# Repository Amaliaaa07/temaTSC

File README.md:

# temaTSC
smartwatch

## BOM (Bill of Materials)

| Referință | Componentă | Descriere | Cantitate | Link JLC | Datasheet |
|-----------|-----------|-------------------|-----------|----------|-----------|
| U1          | MCU             | nRF52840               | 1         | [JLC](https://jlcpcb.com/partdetail/NordicSemiconductor-nRF52840_QIAA/C190794) | [Datasheet](https://4donline.ihs.com/images/VipMasterIC/IC/NRSA/NRSA-S-A0021008244/NRSA-S-A0021008244-1.pdf?hkey=61A2E4C270F0397D049F8F05BD4F1054)  |
| IC1         | LiPo Charger    | BQ25180YBGR            | 1         | [JLC](https://componentsearchengine.com/prices/BQ25180YBGR?manufacturer=Texas%20Instruments)     | [Datasheet](https://www.ti.com/lit/ds/symlink/bq25180.pdf)                                                     |
| IC2         | Haptic Driver   | DRV2605YZFR            | 1         | [JLC](https://componentsearchengine.com/prices/DRV2605YZFR?manufacturer=Texas%20Instruments)     | [Datasheet](https://www.ti.com/lit/ds/symlink/drv2605.pdf)                                                     |
| IC3         | IMU             | BMA423                 | 1         | [JLC](https://componentsearchengine.com/prices/BMA423?manufacturer=BOSCH)                      | [Datasheet](https://4donline.ihs.com/images/VipMasterIC/IC/BSCH/BSCH-S-A0007921771/BSCH-S-A0010021471-1.pdf?hkey=61A2E4C270F0397D049F8F05BD4F1054)    |
| IC9         | DC/DC Converter | RT6160AWSC             | 1         | [JLC](https://componentsearchengine.com/prices/RT6160AWSC?manufacturer=RICHTEK)               | [Datasheet](https://4donline.ihs.com/images/VipMasterIC/IC/RHTK/RHTK-S-A0025617216/RHTK-S-A0025617221-1.pdf?hkey=61A2E4C270F0397D049F8F05BD4F1054)                                |
| U3          | Fuel Gauge      | MAX17048G+T10          | 1         | [JLC](https://componentsearchengine.com/prices/MAX17048G%2BT10?manufacturer=Analog%20Devices)      | [Datasheet](https://4donline.ihs.com/images/VipMasterIC/IC/RHTK/RHTK-S-A0025617216/RHTK-S-A0025617221-1.pdf?hkey=61A2E4C270F0397D049F8F05BD4F1054)         |
| D3          | ESD Protection  | USBLC6-2SC6Y           | 1         | [JLC](https://componentsearchengine.com/prices/USBLC6-2SC6Y?manufacturer=STMicroelectronics)   | [Datasheet](https://www.analog.com/media/en/technical-documentation/data-sheets/MAX17048-MAX17049.pdf?ADICID=SYND_WW_P682800_PF-spglobal)                                             |
| J4          | USB-C Connector | KH-TYPE-C-16P          | 1         | [JLC](https://www.snapeda.com/parts/KH-TYPE-C-16P/kinghelm/view-part/?ref=search&t=KH-TYPE-C-16P&ab_test_case=b)                    | [Datasheet](https://www.snapeda.com/parts/KH-TYPE-C-16P/kinghelm/datasheet/)        |
| J1          | E-Paper Connector | 503480-2400E         | 1         | [JLC](https://componentsearchengine.com/prices/5034802400?manufacturer=Molex)                 | [Datasheet](https://4donline.ihs.com/images/VipMasterIC/IC/MOLE/MOLE-S-A0003522481/MOLE-S-A0010982248-1.pdf?hkey=61A2E4C270F0397D049F8F05BD4F1054)                                      |
| ANT1        | Antena BLE      | 2450AT18B100E          | 1         | [JLC](https://componentsearchengine.com/prices/2450AT18B100E?manufacturer=JOHANSON%20TECHNOLOGY)             | [Datasheet](https://www.johansontechnology.com/docs/1187/2450AT18B100_X8XXogU.pdf)                     |
| X1          | Crystal 32MHz   | SMD 2016               | 1         | [JLC](https://componentsearchengine.com/prices/SMD2016B050TF?manufacturer=Yageo%20Group)                   | [Datasheet](https://4donline.ihs.com/images/VipMasterIC/IC/YAGO/YAGO-S-A0024580626/YAGO-S-A0024591343-1.pdf?hkey=61A2E4C270F0397D049F8F05BD4F1054)                            |
| X2          | Crystal 32.768kHz | SMD 2016             | 1         | [JLC](https://componentsearchengine.com/prices/SMD2016B050TF?manufacturer=Yageo%20Group)               | [Datasheet](https://4donline.ihs.com/images/VipMasterIC/IC/YAGO/YAGO-S-A0024580626/YAGO-S-A0024591343-1.pdf?hkey=61A2E4C270F0397D049F8F05BD4F1054)                               |
| SW1-3       | Buton tactil    | EVP-AKE31A             | 3         | [JLC](https://componentsearchengine.com/prices/EVP-AKE31A?manufacturer=Panasonic)               | [Datasheet](https://industrial.panasonic.com/cdbs/www-data/pdf/ATK0000/ATK0000C434.pdf)                        |
| J2          | SWD Connector   | TC2030-IDC             | 1         | [JLC](https://componentsearchengine.com/prices/TC2030-IDC?manufacturer=Tag%20Connect)             | [Datasheet](https://4donline.ihs.com/images/VipMasterIC/IC/TGCN/TGCN-S-A0008988129/TGCN-S-A0008988129-1.pdf?hkey=61A2E4C270F0397D049F8F05BD4F1054)                   |
| Q2          | MOSFET P-ch     | DMG2305UX-7            | 1         | [JLC](https://componentsearchengine.com/prices/DMG2305UX-7?manufacturer=Diodes%20Incorporated)                 | [Datasheet](https://4donline.ihs.com/images/VipMasterIC/IC/DIOD/DIOD-S-A0013043571/DIOD-S-A0013120650-1.pdf?hkey=61A2E4C270F0397D049F8F05BD4F1054)                                            |
| Q3          | MOSFET N-ch     | SI1308EDL-T1-GE3       | 1         | [JLC](https://componentsearchengine.com/prices/Si1308EDL-T1-GE3?manufacturer=Vishay)             | [Datasheet](https://4donline.ihs.com/images/VipMasterIC/IC/VISH/VISH-S-A0000692786/VISH-S-A0000692786-1.pdf?hkey=61A2E4C270F0397D049F8F05BD4F1054)                                                   |
| D2, D4, D5  | Dioda Schottky  | MBR0530                | 3         | [JLC](https://componentsearchengine.com/prices/MBR0530?manufacturer=MCC)           | [Datasheet](https://4donline.ihs.com/images/VipMasterIC/IC/MCCC/MCCCS04194/MCCCS04194-1.pdf?hkey=61A2E4C270F0397D049F8F05BD4F1054)                                         |
| L1          | Inductanta 0.47µH | FTC252012SR47MBCA    | 1         | [JLC](https://jlcpcb.com/partdetail/6763488-FTC252012SR47MBCA/C5832368)                 |
| L2          | Inductanta 15nH | RF matching 0201       | 1         | [JLC](https://jlcpcb.com/partdetail/Sunlord-SDCL0201C15NJTDF/C389547)          |     -                   |
| L3          | Inductanta 3.9nH | RF matching 0201      | 1         | [JLC](https://jlcpcb.com/partdetail/Sunlord-SDCL0201C3N9STDF/C389544)          |     -                   |
| L5          | Inductanta 68µH | EPD driver SMD         | 1         | [JLC](https://jlcpcb.com/partdetail/Sumida-CDMC4D28NP680MC/C408336)            |     -                       |
| L7          | Inductanta 10µH | DC/DC SMD              | 1         | [JLC](https://jlcpcb.com/partdetail/Sunlord-MWSA0402S100MT/C408352)            |     -                     |
| C*          | Condensatoare   | 100nF decuplare 0201   | multiple  | [JLC](https://jlcpcb.com/partdetail/Samsung-CL03B104KO3NNNC/C15195)            | -                                                                                                               |
| C*          | Condensatoare   | >100nF bulk 0402       | multiple  | [JLC](https://jlcpcb.com/partdetail/Samsung-CL05A475KP5NRNC/C25771)            | -                                                                                                               |
| R*          | Rezistente      | Diverse valori 0201    | multiple  | [JLC](https://jlcpcb.com/partdetail/UNI-ROYAL-0201WAF1001T5E/C17513)           | -                                                                                                               |

## Descrierea funcționalității hardware

### Microcontroller — nRF52840

Inima dispozitivului este **Nordic nRF52840**, un SoC (System on Chip) cu procesor ARM Cortex-M4 la 64 MHz, cu unitate FPU, 1 MB Flash, 256 KB RAM și radio Bluetooth 5.0 integrat. Chipul operează la 3.3V și gestionează toate perifericele prin interfețele SPI, I2C și GPIO.

### Alimentare

Lanțul de alimentare funcționează astfel:
- **USB-C (KH-TYPE-C-16P)** furnizează VBUS (5V) prin conectorul de încărcare
- **USBLC6-2SC6Y** protejează liniile D+/D- împotriva descărcărilor electrostatice (ESD)
- **BQ25180YBGR** este charger-ul LiPo care încarcă bateria de 3.7V și comunică cu MCU-ul prin I2C pentru a raporta starea încărcării. Curentul maxim de încărcare este de 350mA.
- **MAX17048G+T10** este fuel gauge-ul care măsoară tensiunea bateriei și estimează starea de încărcare (SoC) prin algoritmul ModelGauge, comunicând prin I2C. Generează o întrerupere ALERT când bateria scade sub un prag configurat.
- **RT6160AWSC** este un convertor DC/DC boost care generează tensiunea de 3.3V necesară MCU-ului și perifericelor din tensiunea bateriei. Frecvența de comutare este de 1.5MHz, folosind inductanța L7 de 10µH.

### Display E-Paper

Display-ul e-paper se conectează prin conectorul FFC **503480-2400** (24 pini). Interfața de comunicație este **SPI** (MOSI, SCK) împreună cu semnale de control GPIO:
- **EPD_CS** — chip select
- **EPD_DC** — selectare mod Data/Command
- **EPD_RST** — reset display
- **EPD_BUSY** — semnal de ocupat (MCU-ul așteaptă să devină LOW înainte de a trimite date noi)

Circuitul de drive al display-ului conține diode Schottky MBR0530, MOSFET-uri și inductanța L5 (68µH) pentru generarea tensiunilor ridicate necesare panoului e-paper (PREVGH pozitiv, PREVGL negativ). Marele avantaj al display-ului e-paper este consumul zero în standby — imaginea rămâne afișată fără alimentare (display bistabil).

### IMU — BMA421

Senzorul de mișcare **BMA421** de la Bosch este un accelerometru 3-axis cu consum ultra-redus, folosit pentru:
- Detectarea pașilor (pedometru integrat în hardware)
- Recunoașterea activității (mers, alergat, stat)
- Detectarea orientării dispozitivului
- Wake-up la mișcare (trezirea MCU-ului din sleep)

Comunică cu MCU-ul prin **I2C** la adresa 0x18 sau 0x19 (selectabilă prin pinul SDO). Generează întreruperi pe liniile **INT1** și **INT2** pentru a trezi MCU-ul la detectarea unor evenimente, fără a consuma energie în modul standby. Tensiunea de alimentare este 3.3V (VDDIO și VDD).

### Driver Haptic — DRV2605YZFR

**DRV2605YZFR** de la Texas Instruments este un driver pentru actuatoare haptice (LRA/ERM) cu bibliotecă internă de 123 de efecte de vibrație stocate în ROM. Comunică prin **I2C** la adresa 0x5A și este activat de MCU prin semnalul **HAPTIC_EN** (GPIO). Oferă feedback tactil utilizatorului la interacțiunile cu interfața (notificări, confirmare butoane etc.).

### Conectivitate BLE

Radio-ul BLE integrat în nRF52840 operează la 2.4GHz și suportă Bluetooth 5.0 cu rate de date de 1Mbps (LE 1M PHY) și 2Mbps (LE 2M PHY). Este conectat la antena **2450AT18B100E** de la Johanson Technology printr-o rețea de matching RF compusă din L2 (15nH), L3 (3.9nH) și condensatoare de 1pF. Antena este plasată la exteriorul PCB-ului, iar zona de sub antenă este decupată complet (fără cupru și fără trasee) pentru a nu degrada performanța RF.

### Butoane

Trei butoane tactile **EVP-AKE31A** de la Panasonic (SW_UP, SW_DN, SW_ENT) sunt conectate la GPIO-urile MCU-ului cu rezistențe de pull-up de 10kΩ. La apăsare, pinul GPIO este tras la GND. Butoanele sunt plasate pe marginea PCB-ului, aliniate cu orificiile fizice din carcasă.

### Debug SWD

Interfața de programare și depanare **SWD** este expusă prin conectorul **TC2030-IDC** (Tag-Connect 6-pin, fără găuri). Semnalele disponibile sunt SWDIO, SWDCLK, SWO (trace), RESET, 3.3V și GND. Toate sunt marcate pe silkscreen cu test pad-uri dedicate.

### Oscilatoare

- **Crystal 32 MHz** — oscilator principal pentru MCU și radio BLE, cu condensatoare de sarcină de 12pF. Conectat pe pinii dedicați P0.00/XL1 și P0.01/XL2.
- **Crystal 32.768 kHz** — oscilator pentru RTC (Real Time Clock), cu condensatoare de 12pF. Conectat pe pinii dedicați XC1 și XC2. Permite timekeeping precis în modul low power.

---

## Calcul consum de energie

| Componentă | Curent tipic | Mod |
|-----------|-------------|-----|
| nRF52840 | 4.8 mA | Activ CPU |
| nRF52840 | 0.4 µA | Deep sleep |
| nRF52840 | 5.3 mA | BLE advertising |
| BMA421 | 150 µA | Normal |
| BMA421 | 2 µA | Low power |
| DRV2605 | 9 mA | Activ |
| DRV2605 | 40 µA | Standby |
| MAX17048 | 23 µA | Activ |
| RT6160AWSC | ~50 µA | Quiescent |
| Display e-paper | ~26 mA | Refresh |
| Display e-paper | 0 mA | Standby (bistabil) |

**Estimare autonomie:** Cu o baterie LiPo de 200mAh, în modul normal de utilizare (MCU în sleep majoritatea timpului, refresh display de câteva ori pe zi, BLE advertising periodic), curentul mediu estimat este de aproximativ 1-2mA, rezultând o autonomie de **4-8 zile**.

## Pinii nRF52840 utilizați

| Pin nRF52840 | Semnal | Componentă | Interfață | Motiv |
|-------------|--------|-----------|-----------|-------|
| P0.00/XL1 | XL1 | Crystal 32MHz | XTAL | Pin dedicat oscilator principal |
| P0.01/XL2 | XL2 | Crystal 32MHz | XTAL | Pin dedicat oscilator principal |
| XC1, XC2 | - | Crystal 32.768kHz | XTAL | Pini RTC dedicați |
| P0.04 | EPD_CS | E-Paper | SPI CS | Chip select display |
| P0.05 | EPD_DC | E-Paper | GPIO | Data/Command select |
| P0.06 | MOSI | E-Paper | SPI | Date SPI |
| P0.07 | SCK | E-Paper | SPI | Clock SPI |
| P0.08 | EPD_RST | E-Paper | GPIO | Reset display |
| P0.09 | EPD_BUSY | E-Paper | GPIO | Busy signal display |
| P0.13 | D- | USB-C | USB | Linie date USB |
| P0.14 | D+ | USB-C | USB | Linie date USB |
| P0.25 | SDA | I2C bus | I2C | Date I2C (IMU, Haptic, Charger, FuelGauge) |
| P0.26 | SCL | I2C bus | I2C | Clock I2C |
| P0.27 | PMIC_INT | BQ25180 | GPIO | Întrerupere charger |
| P0.28 | ALERT | MAX17048 | GPIO | Alertă fuel gauge |
| P1.01 | HAPTIC_EN | DRV2605 | GPIO | Enable driver haptic |
| P1.02 | IMU_INT1 | BMA421 | GPIO | Întrerupere IMU 1 |
| P1.03 | IMU_INT2 | BMA421 | GPIO | Întrerupere IMU 2 |
| P1.04 | SW_UP | Buton UP | GPIO | Buton sus |
| P1.05 | SW_DN | Buton DOWN | GPIO | Buton jos |
| P1.06 | SW_ENT | Buton ENTER | GPIO | Buton enter |
| P0.18/RESET | RESET | SWD | SWD | Reset MCU |
| SWDCLK | SWDCLK | TC2030-IDC | SWD | Clock debug |
| SWDIO | SWDIO | TC2030-IDC | SWD | Date debug |
| P0.22 | SWO | TC2030-IDC | SWD | Trace output |
| ANT | RF | Antenă BLE | RF | Pin antenă dedicat |
| VBUS | VBUS | USB-C | Power | Detecție VBUS |

---

## Design log

### Probleme întâmpinate și decizii luate

**Erori Overlap (12) — Aprobate**: Cele 12 erori de overlap 
sunt de trei tipuri:

**Via-Smd Overlap (2)**: Via-uri care se suprapun ușor 
  cu pad-uri SMD în zone aglomerate ale PCB-ului. Mutarea 
  acestora ar compromite rutarea semnalelor din zonă.

**Solid Polygon Shape-Pad Overlap (2)**: Pad-ul 
  termal al unui circuit integrat se suprapune ușor 
  cu conturul (courtyard) componentei vecine. 
  Suprapunerea este minimă și nu afectează 
  funcționalitatea electrică sau asamblarea, 
  deoarece componentele nu se suprapun fizic.

**Smd-Via Overlap (6)**: Via-uri plasate în apropierea 
  pad-urilor SMD în zone aglomerate ale PCB-ului. Acestea 
  sunt necesare pentru rutarea semnalelor și nu pot fi 
  mutate fără a compromite rutarea generală. Suprapunerea 
  este minimă și nu afectează funcționalitatea electrică 
  sau procesul de fabricație.

**Modelele 3D**
Componentele mici (rezistențe 0201, condensatoare 0201/0402) nu au modele 3D individuale asociate și folosesc modelul generic din Fusion 360. Componentele principale (nRF52840, BQ25180, conectorul USB-C, butoanele, cristalele) au modele 3D reale asociate.

---

## Imagini

Randările PCB-ului și ale dispozitivului complet se găsesc în folderul `/Images`.

---

## Licență

Acest proiect este licențiat sub licența **Apache 2.0**. Vezi fișierul [LICENSE](LICENSE) pentru detalii.

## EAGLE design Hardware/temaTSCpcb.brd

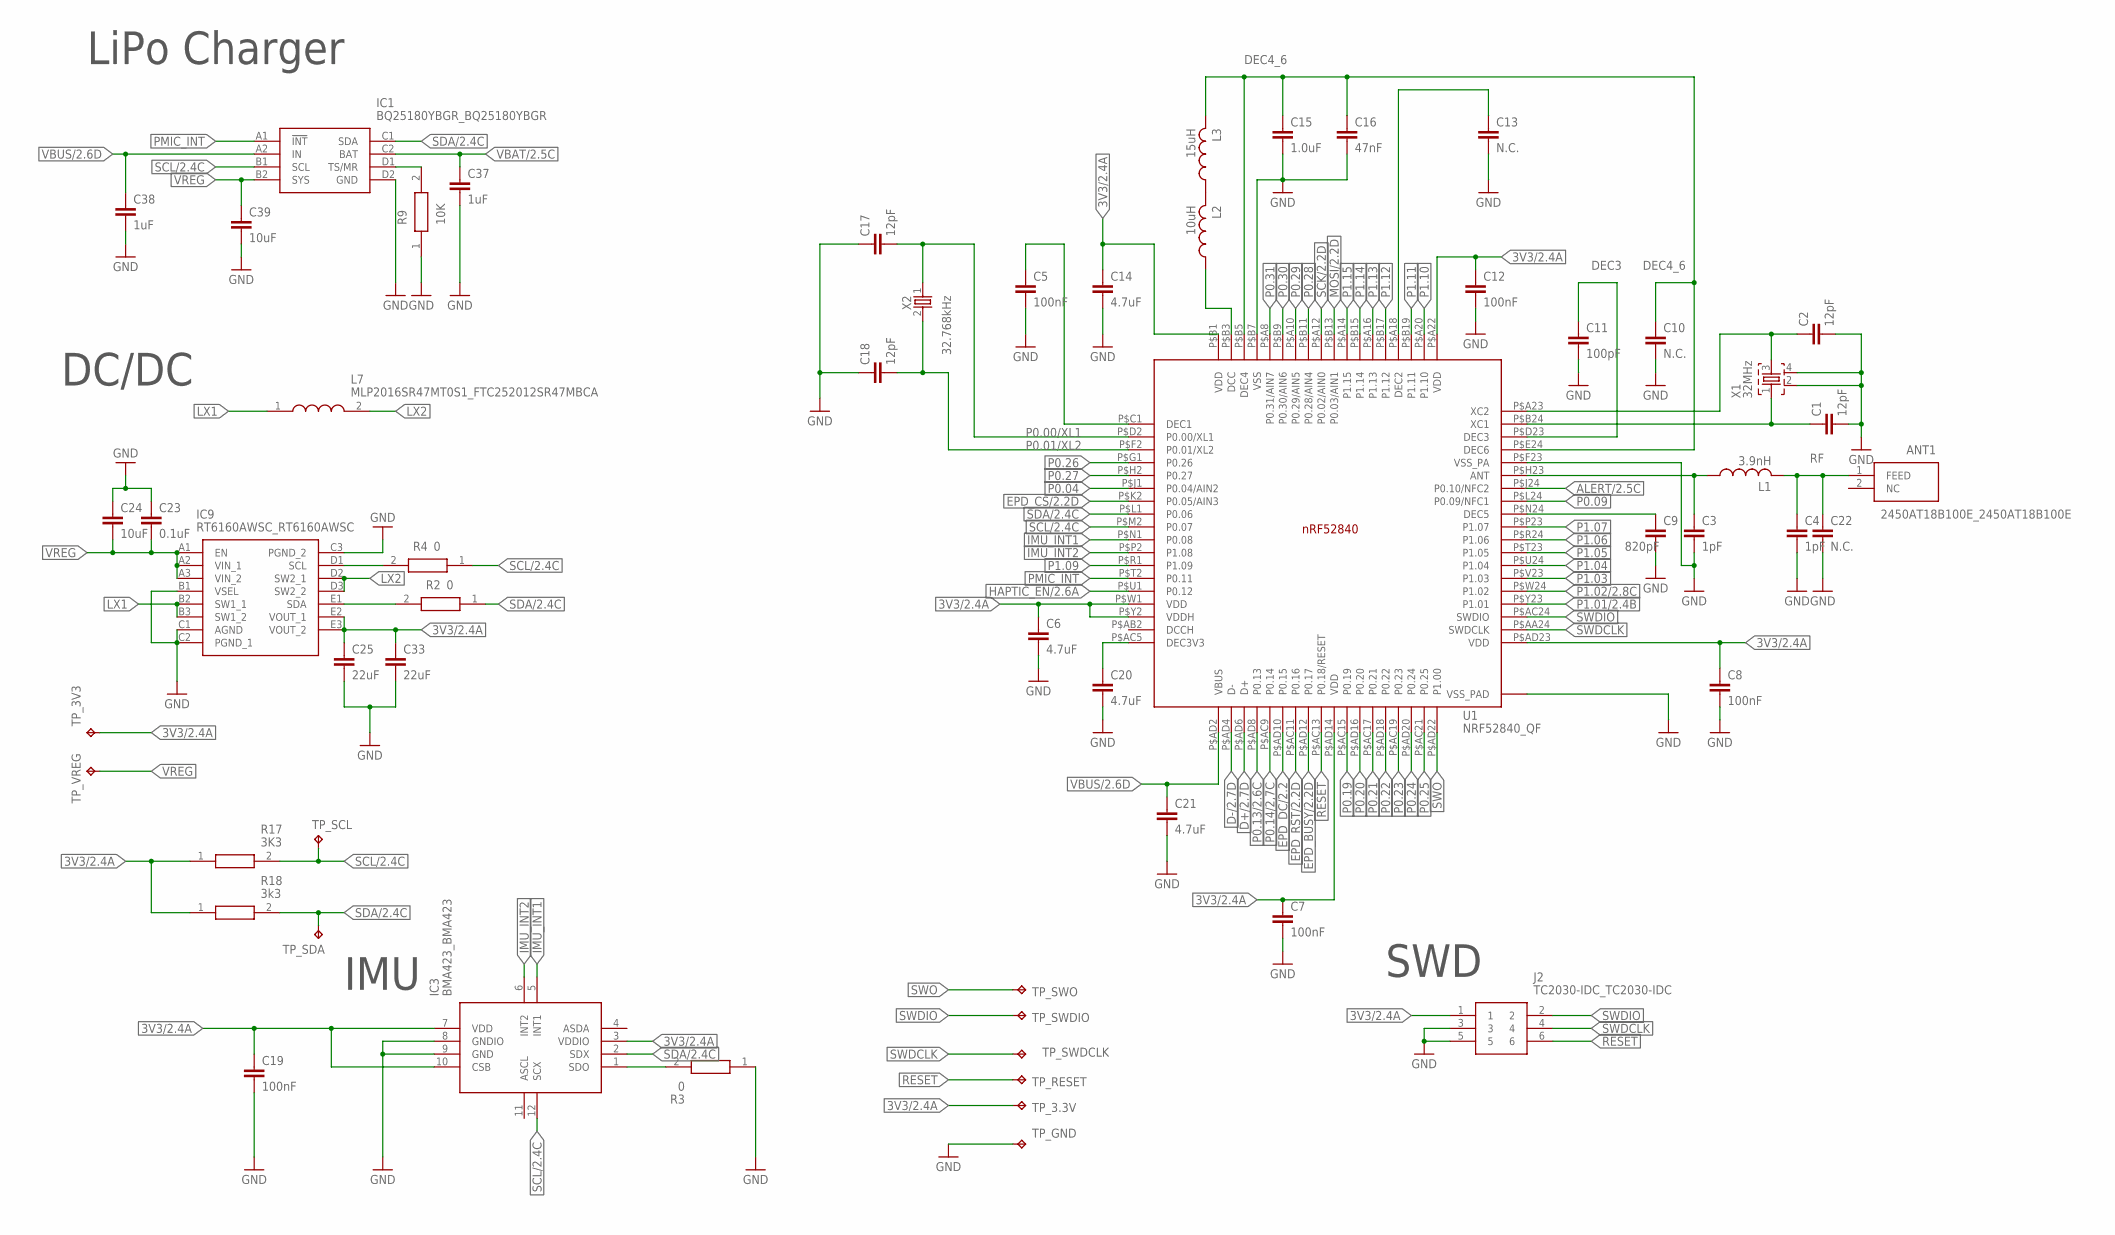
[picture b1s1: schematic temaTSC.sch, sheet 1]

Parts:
ANT1: 2450AT18B100E_2450AT18B100E; 2450AT18B100E_ANTC3216X140N
C1, C2, C17, C18: 12pF; NORDIC_NRF_3_RESC0201_L
C3, C4: 1pF; NORDIC_NRF_3_RESC0201_L
C5, C7, C8, C12, C19: 100nF; NORDIC_NRF_3_RESC0201_L
C6, C14, C20, C21: 4.7uF; NORDIC_NRF_3_RESC0402_L
C9: 820pF; NORDIC_NRF_3_RESC0201_L
C10, C13, C22: N.C.; NORDIC_NRF_3_RESC0201_L
C11: 100pF; NORDIC_NRF_3_RESC0201_L
C15: 1.0uF; NORDIC_NRF_3_RESC0402_L
C16: 47nF; NORDIC_NRF_3_RESC0201_L
C23: 0.1uF; NORDIC_NRF_3_RESC0201_L
C24, C39: 10uF; NORDIC_NRF_3_RESC0402_L
C25, C33: 22uF; NORDIC_NRF_3_RESC0402_L
C37, C38: 1uF; NORDIC_NRF_3_RESC0402_L
IC1: BQ25180YBGR_BQ25180YBGR; BQ25180YBGR_BGA8C40P2X4_100X155X50
IC3: BMA423_BMA423
IC9: RT6160AWSC_RT6160AWSC; RT6160AWSC_BGA15C40P3X5_140X230X60
J2: TC2030-IDC_TC2030-IDC; TC2030-IDC_TC2030IDC
L1: 3.9nH; NORDIC_NRF_2_RESC0402_L
L2: 10uH; NORDIC_NRF_2_RESC0402_L
L3: 15uH; NORDIC_NRF_2_RESC0402_L
L7: MLP2016SR47MT0S1_FTC252012SR47MBCA; MLP2016SR47MT0S1_INDC2016X100N
R2, R3, R4: 0; ERA-1AEB3401C_0201
R9: 10K; ERA-1AEB3401C_0201
R17: 3K3; ERA-1AEB3401C_0201
R18: 3k3; ERA-1AEB3401C_0201
TP_3.3V, TP_3V3: HECTOR_WATCH_1_TPTP20R; HECTOR_WATCH_1_TP20R
TP_GND: HECTOR_WATCH_1_TPTP20R; HECTOR_WATCH_1_TP20R
TP_RESET: HECTOR_WATCH_1_TPTP20R; HECTOR_WATCH_1_TP20R
TP_SCL: HECTOR_WATCH_1_TPTP20R; HECTOR_WATCH_1_TP20R
TP_SDA: HECTOR_WATCH_1_TPTP20R; HECTOR_WATCH_1_TP20R
TP_SWDCLK: HECTOR_WATCH_1_TPTP20R; HECTOR_WATCH_1_TP20R
TP_SWDIO: HECTOR_WATCH_1_TPTP20R; HECTOR_WATCH_1_TP20R
TP_SWO: HECTOR_WATCH_1_TPTP20R; HECTOR_WATCH_1_TP20R
TP_VREG: HECTOR_WATCH_1_TPTP20R; HECTOR_WATCH_1_TP20R
U1: NRF52840_QF; NORDIC_NRF_4_AQFN50P700X700X85_HS-74N
X1: 32MHz; NORDIC_NRF_BT-XTAL_2016_N
X2: 32.768kHz; NORDIC_NRF_1_XTAL_3215_N

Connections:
3V3/2.4A: C6.1, C7.1, C8.1, C12.1, C14.1, C19.1, C25.1, C33.1, IC3.3 (VDDIO), IC3.7 (VDD), IC3.10 (CSB), IC9.E2 (VOUT_1), IC9.E3 (VOUT_2), J2.1, R17.1, R18.1, TP_3.3V.TP, TP_3V3.TP, U1.P$A22 (VDD), U1.P$AD14 (VDD), U1.P$AD23 (VDD), U1.P$B1 (VDD), U1.P$W1 (VDD), U1.P$Y2 (VDDH)
ALERT/2.5C: U1.P$J24 (P0.10/NFC2)
D+/2.7D: U1.P$AD6 (D+)
D-/2.7D: U1.P$AD4 (D-)
DEC3: C11.1, U1.P$D23 (DEC3)
DEC4_6: C10.1, C15.1, C16.1, L3.2, U1.P$B5 (DEC4), U1.P$E24 (DEC6)
EPD_BUSY/2.2D: U1.P$AD12 (P0.17)
EPD_CS/2.2D: U1.P$K2 (P0.05/AIN3)
EPD_DC/2.2: U1.P$AD10 (P0.15)
EPD_RST/2.2D: U1.P$AC11 (P0.16)
GND: C1.2, C2.2, C3.2, C4.2, C5.2, C6.2, C7.2, C8.2, C9.2, C10.2, C11.2, C12.2, C13.2, C14.2, C15.2, C16.2, C17.1, C18.1, C19.2, C20.2, C21.2, C22.2, C23.1, C24.1, C25.2, C33.2, C37.2, C38.2, C39.2, IC1.D2 (GND), IC3.8 (GNDIO), IC3.9 (GND), IC9.B1 (VSEL), IC9.C1 (AGND), IC9.C2 (PGND_1), IC9.C3 (PGND_2), J2.3, J2.5, R3.1, R9.1, TP_GND.TP, U1.P$74 (VSS_PAD), U1.P$75 (VSS_PAD), U1.P$76 (VSS_PAD), U1.P$77 (VSS_PAD), U1.P$78 (VSS_PAD), U1.P$79 (VSS_PAD), U1.P$80 (VSS_PAD), U1.P$81 (VSS_PAD), U1.P$82 (VSS_PAD), U1.P$83 (VSS_PAD), U1.P$84 (VSS_PAD), U1.P$85 (VSS_PAD), U1.P$86 (VSS_PAD), U1.P$87 (VSS_PAD), U1.P$88 (VSS_PAD), U1.P$89 (VSS_PAD), U1.P$90 (VSS_PAD), U1.P$B7 (VSS), U1.P$F23 (VSS_PA), X1.2, X1.4; also elsewhere on the board
HAPTIC_EN/2.6A: U1.P$U1 (P0.12)
IMU_INT1: IC3.5 (INT1), U1.P$N1 (P0.08)
IMU_INT2: IC3.6 (INT2), U1.P$P2 (P1.08)
LX1: IC9.B2 (SW1_1), IC9.B3 (SW1_2), L7.1
LX2: IC9.D2 (SW2_1), IC9.D3 (SW2_2), L7.2
MOSI/2.2D: U1.P$B13 (P0.03/AIN1)
unnamed: C5.1, U1.P$C1 (DEC1)
unnamed: L2.1, U1.P$B3 (DCC)
unnamed: IC1.D1 (TS/MR), R9.2
unnamed: IC9.D1 (SCL), R4.2
unnamed: C3.1, L1.1, U1.P$H23 (ANT)
unnamed: IC9.E1 (SDA), R2.2
unnamed: C1.1, U1.P$B24 (XC1), X1.1
unnamed: C2.1, U1.P$A23 (XC2), X1.3
unnamed: C20.1, U1.P$AC5 (DEC3V3)
unnamed: IC3.1 (SDO), R3.2
unnamed: L2.2, L3.1
unnamed: C9.1, U1.P$N24 (DEC5)
unnamed: C13.1, U1.P$A18 (DEC2)
P0.00/XL1: C17.2, U1.P$D2 (P0.00/XL1), X2.1
P0.01/XL2: C18.2, U1.P$F2 (P0.01/XL2), X2.2
P0.04: U1.P$J1 (P0.04/AIN2)
P0.09: U1.P$L24 (P0.09/NFC1)
P0.13/2.6C: U1.P$AD8 (P0.13)
P0.14/2,7C: U1.P$AC9 (P0.14)
P0.19: U1.P$AC15 (P0.19)
P0.20: U1.P$AD16 (P0.20)
P0.21: U1.P$AC17 (P0.21)
P0.22: U1.P$AD18 (P0.22)
P0.23: U1.P$AC19 (P0.23)
P0.24: U1.P$AD20 (P0.24)
P0.25: U1.P$AC21 (P0.25)
P0.26: U1.P$G1 (P0.26)
P0.27: U1.P$H2 (P0.27)
P0.28: U1.P$B11 (P0.28/AIN4)
P0.29: U1.P$A10 (P0.29/AIN5)
P0.30: U1.P$B9 (P0.30/AIN6)
P0.31: U1.P$A8 (P0.31/AIN7)
P1.01/2.4B: U1.P$Y23 (P1.01)
P1.02/2.8C: U1.P$W24 (P1.02)
P1.03: U1.P$V23 (P1.03)
P1.04: U1.P$U24 (P1.04)
P1.05: U1.P$T23 (P1.05)
P1.06: U1.P$R24 (P1.06)
P1.07: U1.P$P23 (P1.07)
P1.09: U1.P$R1 (P1.09)
P1.10: U1.P$A20 (P1.10)
P1.11: U1.P$B19 (P1.11)
P1.12: U1.P$B17 (P1.12)
P1.13: U1.P$A16 (P1.13)
P1.14: U1.P$B15 (P1.14)
P1.15: U1.P$A14 (P1.15)
PMIC_INT: IC1.A1 (!INT), U1.P$T2 (P0.11)
RESET: J2.6, TP_RESET.TP, U1.P$AC13 (P0.18/RESET)
RF: ANT1.1 (FEED), C4.1, C22.1, L1.2
SCK/2.2D: U1.P$A12 (P0.02/AIN0)
SCL/2.4C: IC1.B1 (SCL), IC3.12 (SCX), R4.1, R17.2, TP_SCL.TP, U1.P$M2 (P0.07)
SDA/2.4C: IC1.C1 (SDA), IC3.2 (SDX), R2.1, R18.2, TP_SDA.TP, U1.P$L1 (P0.06)
SWDCLK: J2.4, TP_SWDCLK.TP, U1.P$AA24 (SWDCLK)
SWDIO: J2.2, TP_SWDIO.TP, U1.P$AC24 (SWDIO)
SWO: TP_SWO.TP, U1.P$AD22 (P1.00)
VBAT/2.5C: C37.1, IC1.C2 (BAT)
VBUS/2.6D: C21.1, C38.1, IC1.A2 (IN), U1.P$AD2 (VBUS)
VREG: C23.2, C24.2, C39.1, IC1.B2 (SYS), IC9.A1 (EN), IC9.A2 (VIN_1), IC9.A3 (VIN_2), TP_VREG.TP

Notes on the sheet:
LiPo Charger
DC/DC
IMU
SWD

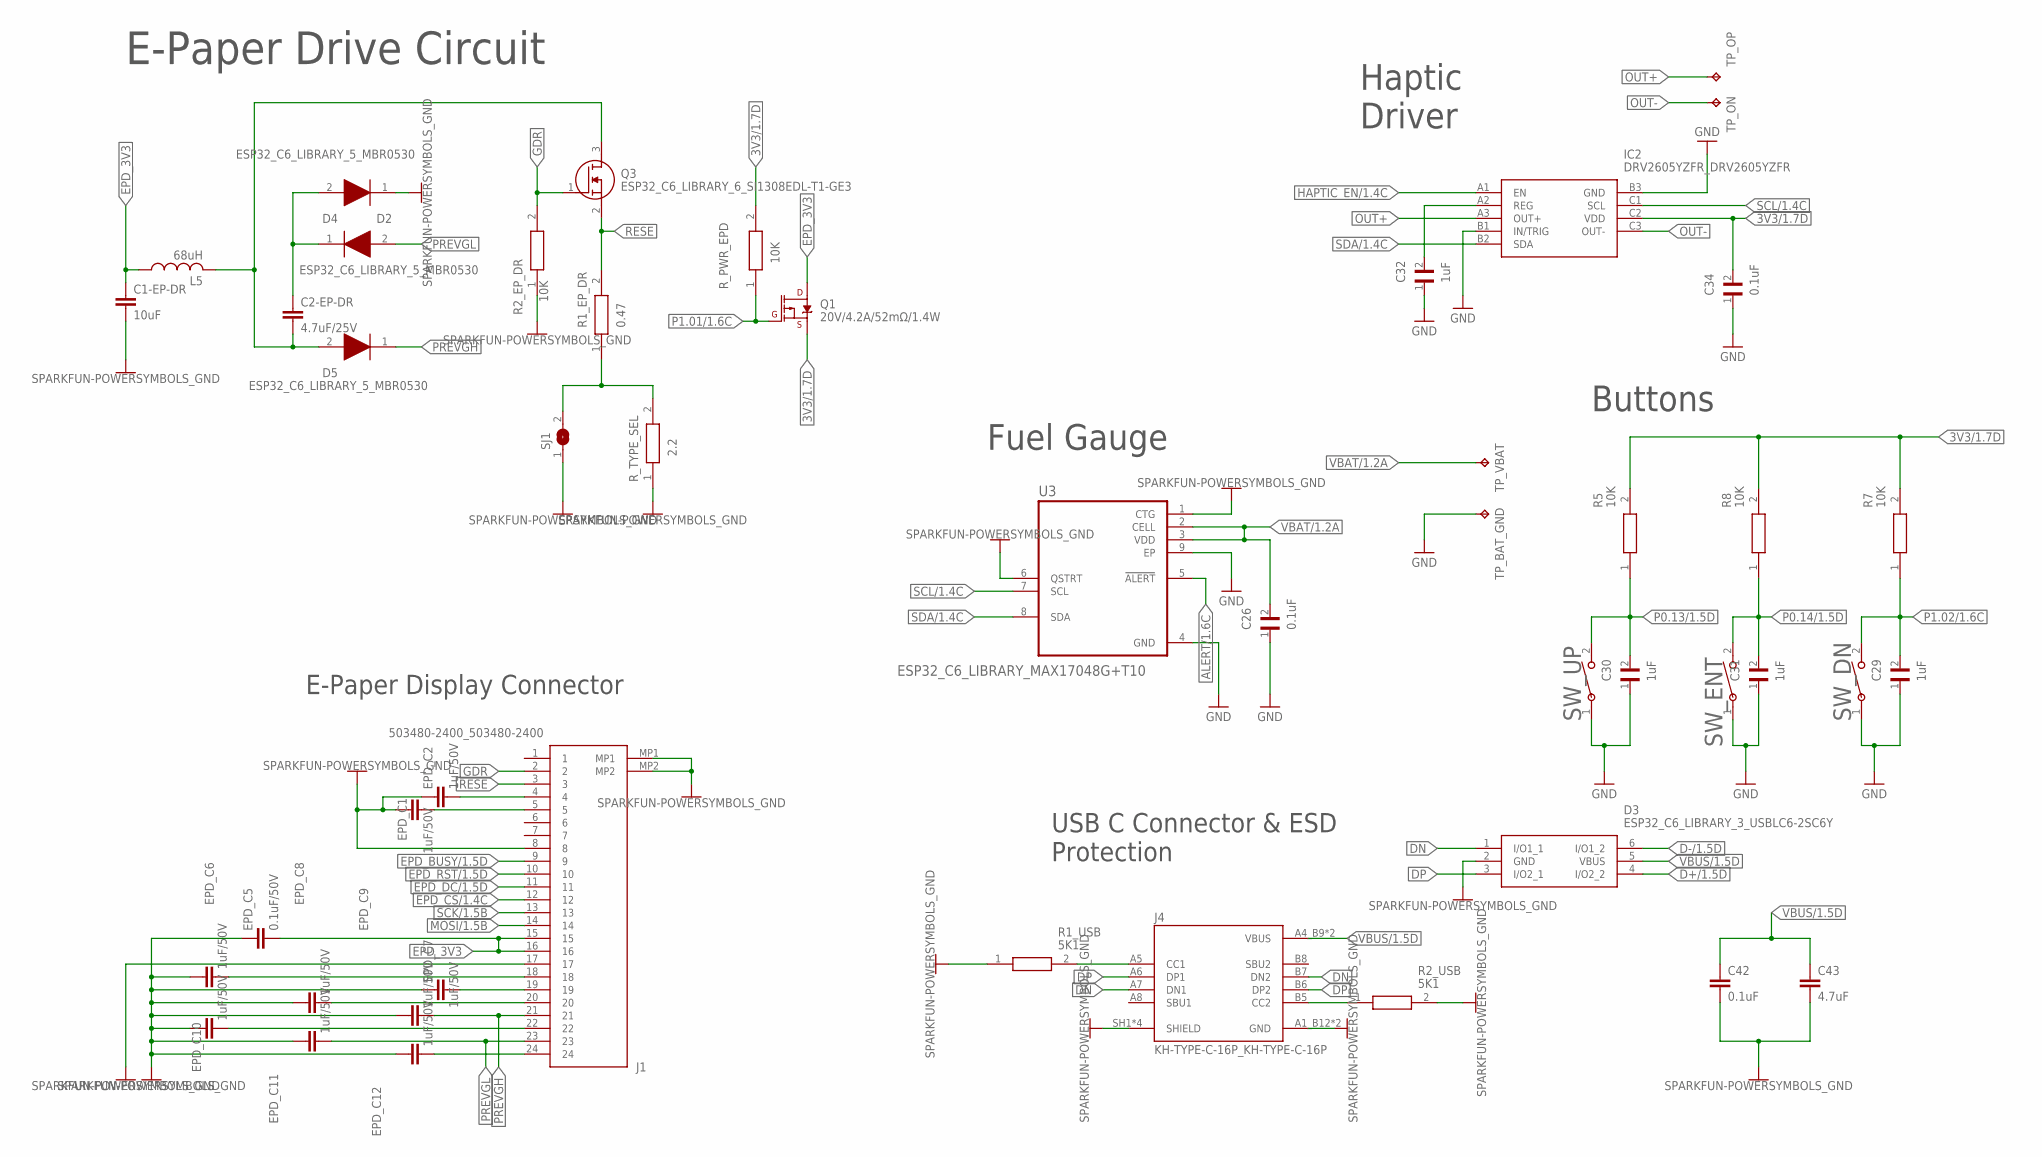
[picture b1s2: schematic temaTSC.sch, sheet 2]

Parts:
C1-EP-DR: 10uF; NORDIC_NRF_3_RESC0402_L
C2-EP-DR: 4.7uF/25V; NORDIC_NRF_3_RESC0402_L
C26, C34: 0.1uF; GRM011R60J152KE01L_1_0201
C29, C30, C31, C32: 1uF; GRM011R60J152KE01L_1_0201
C42: 0.1uF; NORDIC_NRF_3_RESC0201_L
C43: 4.7uF; NORDIC_NRF_3_RESC0402_L
D2, D4, D5: ESP32_C6_LIBRARY_5_MBR0530; ESP32_C6_LIBRARY_5_SOD3716X135N
D3: ESP32_C6_LIBRARY_3_USBLC6-2SC6Y; ESP32_C6_LIBRARY_3_SOT95P280X145-6N
EPD_C1, EPD_C2, EPD_C6, EPD_C7, EPD_C8, EPD_C9, EPD_C10, EPD_C11, EPD_C12: 1uF/50V; NORDIC_NRF_3_RESC0402_L
EPD_C5: 0.1uF/50V; NORDIC_NRF_3_RESC0201_L
IC2: DRV2605YZFR_DRV2605YZFR; DRV2605YZFR_BGA9C50P3X3_144X144X62
J1: 503480-2400_503480-2400; 503480-2400_5034802400
J4: KH-TYPE-C-16P_KH-TYPE-C-16P; KH-TYPE-C-16P_KINGHELM_KH-TYPE-C-16P
L5: 68uH; NORDIC_NRF_2_RESC0402_L
Q1: 20V/4.2A/52mΩ/1.4W; ESP32_C6_LIBRARY_4_ESP32_C6_LIBRARY_4_ESP32_C6_LIBRARY_4_ES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
Q3: ESP32_C6_LIBRARY_6_SI1308EDL-T1-GE3; ESP32_C6_LIBRARY_6_SOT65P210X110-3N
R1_EP_DR: 0.47; ERA-1AEB3401C_0201
R1_USB, R2_USB: 5K1; ERA-1AEB3401C_0201
R2_EP_DR, R5, R7, R8: 10K; ERA-1AEB3401C_0201
R_PWR_EPD: 10K; ERA-1AEB3401C_0201
R_TYPE_SEL: 2.2; ERA-1AEB3401C_0201
SJ1: ESP32_C6_LIBRARY_7_JUMPER_SJ
SW_DN: 2025-10-22_07-23-44_LIBRARY_EVP-AKE31ASW_EVP-AKE3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; 2025-10-22_07-23-44_LIBRARY_SW_EVP-AKE31A_PAN
SW_ENT: 2025-10-22_07-23-44_LIBRARY_EVP-AKE31ASW_EVP-AKE3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; 2025-10-22_07-23-44_LIBRARY_SW_EVP-AKE31A_PAN
SW_UP: 2025-10-22_07-23-44_LIBRARY_EVP-AKE31ASW_EVP-AKE3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; 2025-10-22_07-23-44_LIBRARY_SW_EVP-AKE31A_PAN
TP_BAT_GND: HECTOR_WATCH_1_TPTP20R; HECTOR_WATCH_1_TP20R
TP_ON: HECTOR_WATCH_1_TPTP20R; HECTOR_WATCH_1_TP20R
TP_OP: HECTOR_WATCH_1_TPTP20R; HECTOR_WATCH_1_TP20R
TP_VBAT: HECTOR_WATCH_1_TPTP20R; HECTOR_WATCH_1_TP20R
U3: ESP32_C6_LIBRARY_MAX17048G+T10; ESP32_C6_LIBRARY_SON50P200X200X80-9N

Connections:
3V3/1.7D: C34.2, IC2.C2 (VDD), Q1.2 (S), R5.2, R7.2, R8.2, R_PWR_EPD.2
ALERT/1.6C: U3.5 (!ALERT)
D+/1.5D: D3.4 (I/O2_2)
D-/1.5D: D3.6 (I/O1_2)
DN: D3.1 (I/O1_1), J4.A7 (DN1), J4.B7 (DN2)
DP: D3.3 (I/O2_1), J4.A6 (DP1), J4.B6 (DP2)
EPD_3V3: C1-EP-DR.1, EPD_C5.2, J1.15, J1.16, L5.1, Q1.3 (D)
EPD_BUSY/1.5D: J1.9
EPD_CS/1.4C: J1.12
EPD_DC/1.5D: J1.11
EPD_RST/1.5D: J1.10
GDR: J1.2, Q3.1 (G), R2_EP_DR.2
GND: C1-EP-DR.2, C26.1, C29.1, C30.1, C31.1, C32.1, C34.1, C42.2, C43.2, D3.2 (GND), D4.1 (K), EPD_C1.1, EPD_C2.1, EPD_C5.1, EPD_C6.1, EPD_C7.1, EPD_C8.1, EPD_C9.1, EPD_C10.1, EPD_C11.1, EPD_C12.1, IC2.B1 (IN/TRIG), IC2.B3 (GND), J1.8, J1.17, J1.MP1, J1.MP2, J4.A1_B12 (GND), J4.A12_B1 (GND), J4.SH1 (SHIELD), J4.SH2 (SHIELD), J4.SH3 (SHIELD), J4.SH4 (SHIELD), R1_USB.1, R2_EP_DR.1, R2_USB.2, R_TYPE_SEL.1, SJ1.1, SW_DN.1, SW_ENT.1, SW_UP.1, TP_BAT_GND.TP, U3.1 (CTG), U3.4 (GND), U3.6 (QSTRT), U3.9 (EP); also elsewhere on the board
HAPTIC_EN/1.4C: IC2.A1 (EN)
MOSI/1.5B: J1.14
unnamed: C2-EP-DR.2, D5.2 (A), L5.2, Q3.3 (D)
unnamed: EPD_C6.2, J1.18
unnamed: C2-EP-DR.1, D2.1 (K), D4.2 (A)
unnamed: EPD_C7.2, J1.19
unnamed: EPD_C2.2, J1.4
unnamed: EPD_C1.2, J1.5
unnamed: EPD_C8.2, J1.20
unnamed: R1_EP_DR.1, R_TYPE_SEL.2, SJ1.2
unnamed: EPD_C10.2, J1.22
unnamed: EPD_C12.2, J1.24
unnamed: J4.B5 (CC2), R2_USB.1
unnamed: C32.2, IC2.A2 (REG)
unnamed: J4.A5 (CC1), R1_USB.2
OUT+: IC2.A3 (OUT+), TP_OP.TP
OUT-: IC2.C3 (OUT-), TP_ON.TP
P0.13/1.5D: C30.2, R5.1, SW_UP.2
P0.14/1.5D: C31.2, R8.1, SW_ENT.2
P1.01/1.6C: Q1.1 (G), R_PWR_EPD.1
P1.02/1.6C: C29.2, R7.1, SW_DN.2
PREVGH: D5.1 (K), EPD_C9.2, J1.21
PREVGL: D2.2 (A), EPD_C11.2, J1.23
RESE: J1.3, Q3.2 (S), R1_EP_DR.2
SCK/1.5B: J1.13
SCL/1.4C: IC2.C1 (SCL), U3.7 (SCL)
SDA/1.4C: IC2.B2 (SDA), U3.8 (SDA)
VBAT/1.2A: C26.2, TP_VBAT.TP, U3.2 (CELL), U3.3 (VDD)
VBUS/1.5D: C42.1, C43.1, D3.5 (VBUS), J4.A4_B9 (VBUS), J4.A9_B4 (VBUS)

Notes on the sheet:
E-Paper Drive Circuit
Haptic Driver
Buttons
Fuel Gauge
E-Paper Display Connector
USB C Connector & ESD Protection

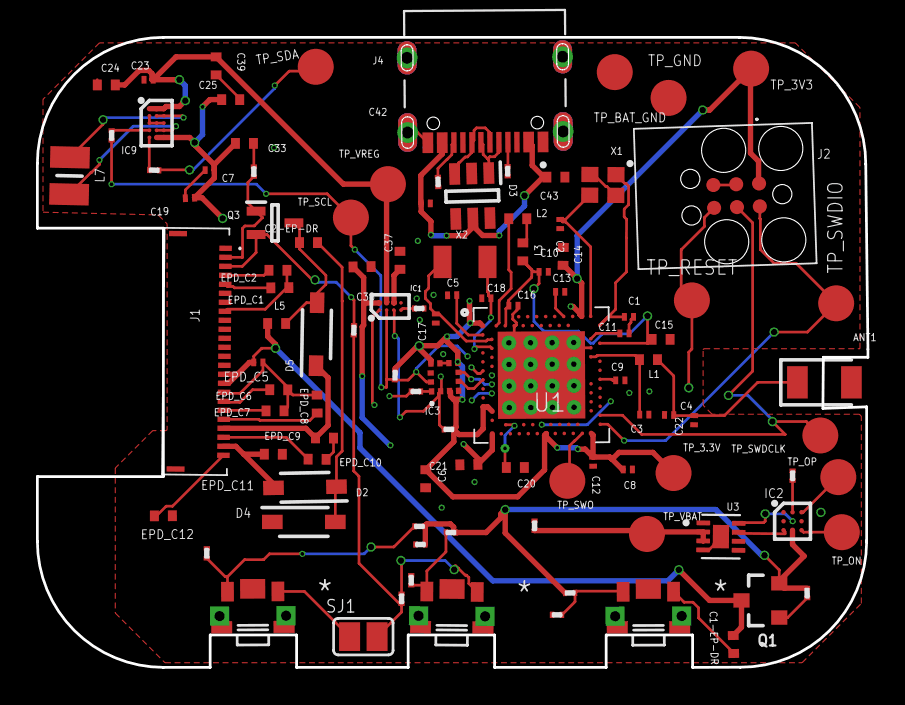
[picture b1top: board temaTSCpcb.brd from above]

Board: 4 copper layers, 46.1 x 35.0 mm, 105 parts (0 on the bottom side), 65 nets.

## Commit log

2026-04-10 Add image to README for visual enhancement
2026-04-16 improvement for error details
    Updated the design log section with detailed explanations of various approved errors and overlaps encountered during PCB design, including specific types and their implications for functionality and 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
2026-04-16 Fix datasheet link for BLE antenna
    Updated the datasheet link for the BLE antenna.
2026-04-16 schematic dupa review
2026-04-16 pcb dupa review
2026-04-21 mechanical final
2026-04-22 Add STEP file

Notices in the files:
parts and their libraries:
InkTime_v5: COPYRIGHT: Copyright (C) 2025 Ultra Librarian. All rights reserved.
